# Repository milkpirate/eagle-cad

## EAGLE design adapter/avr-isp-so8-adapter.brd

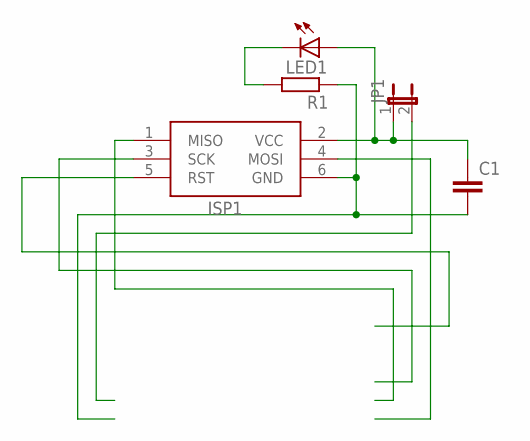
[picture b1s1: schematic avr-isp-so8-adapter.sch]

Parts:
C1: C-EUC0805K; C0805K
ISP1: AVRISP-6; AVRISP
JP1: JUMPER-2SMD-NO; SJ_2S-NO
LED1: LEDCHIPLED_0805; CHIPLED_0805
R1: R-EU_R0805; R0805

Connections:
unnamed: C1.2, ISP1.6 (GND), R1.1
unnamed: LED1.C, R1.2
VCC: C1.1, ISP1.2 (VCC), JP1.1, LED1.A

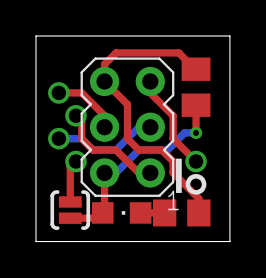
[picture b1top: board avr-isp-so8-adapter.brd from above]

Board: 2 copper layers, 10.8 x 11.4 mm, 5 parts (0 on the bottom side), 3 nets.

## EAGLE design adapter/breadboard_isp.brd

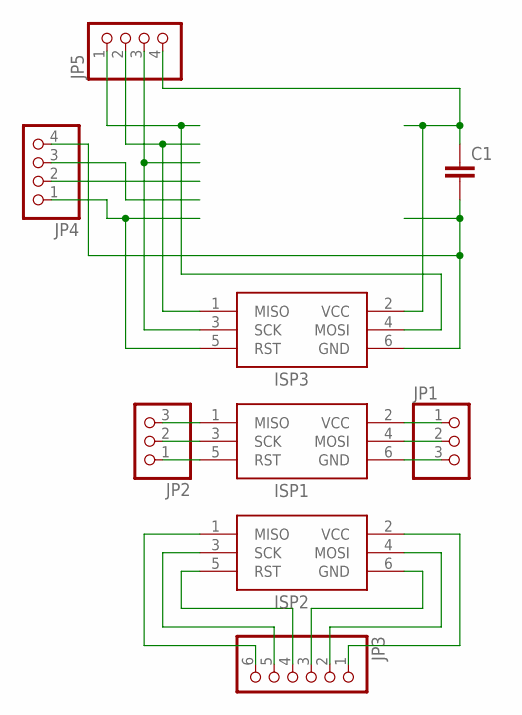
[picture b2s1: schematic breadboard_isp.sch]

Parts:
C1: C-EU025-025X050; C025-025X050
ISP1, ISP2, ISP3: AVRISP-6; AVRISP
JP1, JP2: PINHD-1X3; 1X03
JP3: PINHD-1X6; 1X06
JP4, JP5: PINHD-1X4; 1X04

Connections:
unnamed: ISP1.5 (RST), JP2.1
unnamed: ISP1.3 (SCK), JP2.2
unnamed: ISP1.1 (MISO), JP2.3
unnamed: ISP1.2 (VCC), JP1.1
unnamed: ISP1.4 (MOSI), JP1.2
unnamed: ISP1.6 (GND), JP1.3
unnamed: ISP2.5 (RST), JP3.4
unnamed: ISP2.6 (GND), JP3.3
unnamed: ISP2.4 (MOSI), JP3.2
unnamed: ISP2.3 (SCK), JP3.5
unnamed: ISP2.1 (MISO), JP3.6
unnamed: ISP2.2 (VCC), JP3.1
unnamed: C1.1, ISP3.2 (VCC), JP5.4
unnamed: C1.2, ISP3.6 (GND), JP4.4
unnamed: ISP3.4 (MOSI), JP5.1
unnamed: ISP3.1 (MISO), JP5.2
unnamed: ISP3.3 (SCK), JP5.3
unnamed: ISP3.5 (RST), JP4.1

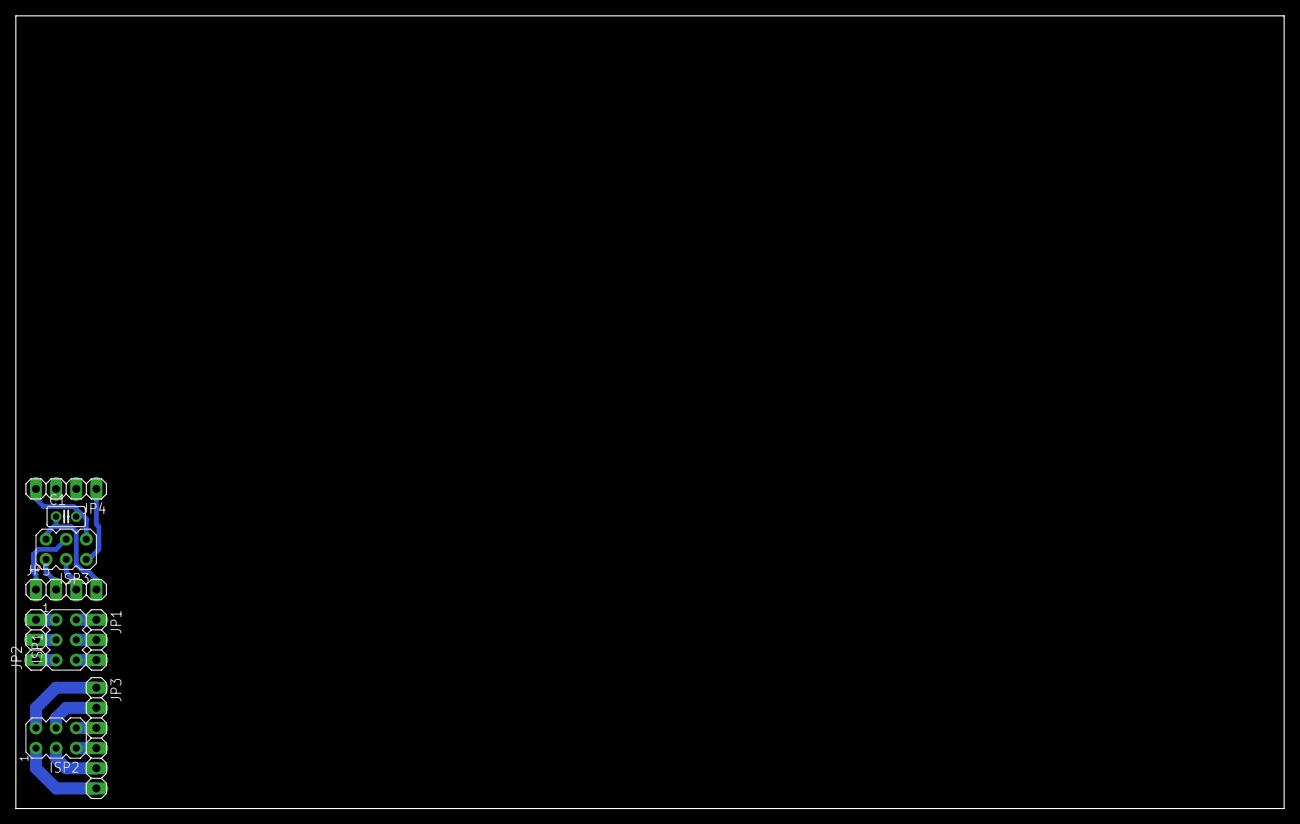
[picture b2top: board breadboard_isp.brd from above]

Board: 2 copper layers, 160.0 x 100.0 mm, 9 parts (0 on the bottom side), 18 nets.

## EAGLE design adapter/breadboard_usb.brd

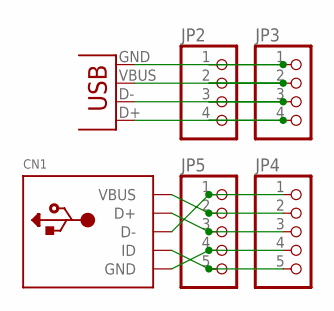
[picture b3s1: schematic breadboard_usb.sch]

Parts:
CN1: USBTHM; USB-MINIB-THM
JP1: USB-B; USB-B-PTH
JP2, JP3: PINHD-1X4; 1X04
JP4, JP5: PINHD-1X5; 1X05

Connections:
D+: CN1.D+, JP4.3, JP5.3
D-: CN1.D-, JP4.1, JP5.1
GND: CN1.GND, JP4.4, JP5.4
ID: CN1.ID, JP4.5, JP5.5
unnamed: JP1.GND, JP2.1, JP3.1
unnamed: JP1.VBUS, JP2.2, JP3.2
unnamed: JP1.D-, JP2.3, JP3.3
unnamed: JP1.D+, JP2.4, JP3.4
VUSB: CN1.VBUS, JP4.2, JP5.2

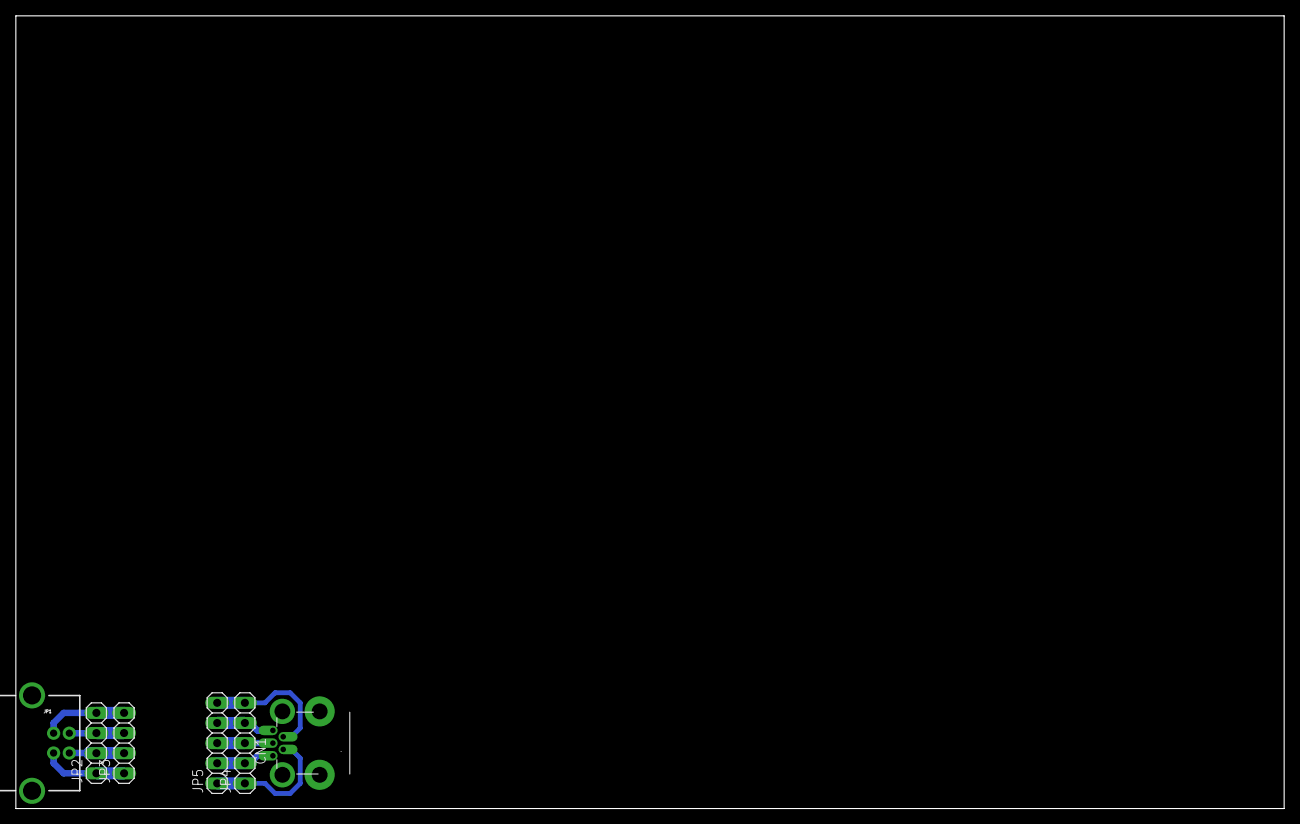
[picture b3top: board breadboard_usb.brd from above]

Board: 2 copper layers, 160.0 x 100.0 mm, 6 parts (0 on the bottom side), 9 nets.

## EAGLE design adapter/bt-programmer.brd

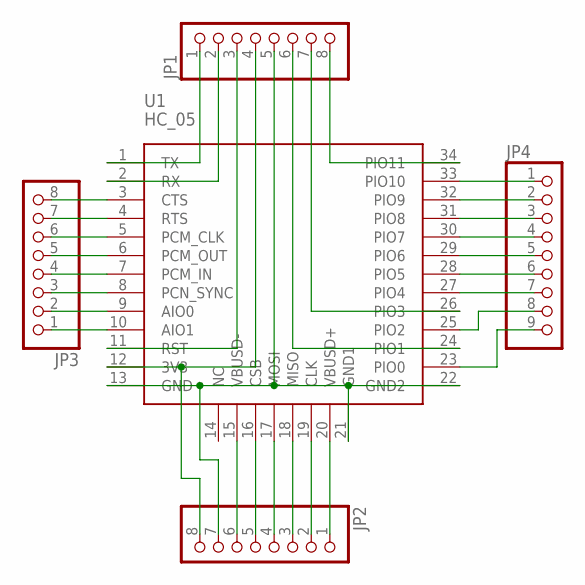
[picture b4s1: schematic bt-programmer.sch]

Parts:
JP1, JP2, JP3: PINHD-1X8; 1X08
JP4: PINHD-1X9; 1X09
U1: HC_05; BLUETOOTH_SMD

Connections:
unnamed: JP1.1, U1.1 (TX)
unnamed: JP1.2, U1.2 (RX)
unnamed: JP1.4, JP2.8, U1.12 (3V3)
unnamed: JP1.5, JP2.7, U1.13 (GND), U1.21 (GND1), U1.22 (GND2)
unnamed: JP1.3, U1.11 (RST)
unnamed: JP1.8, U1.34 (PIO11)
unnamed: JP1.7, U1.26 (PIO3)
unnamed: JP1.6, U1.24 (PIO1)
unnamed: JP2.6, U1.15 (VBUSD-)
unnamed: JP2.5, U1.16 (CSB)
unnamed: JP2.4, U1.17 (MOSI)
unnamed: JP2.3, U1.18 (MISO)
unnamed: JP2.2, U1.19 (CLK)
unnamed: JP2.1, U1.20 (VBUSD+)
unnamed: JP3.1, U1.10 (AIO1)
unnamed: JP3.2, U1.9 (AIO0)
unnamed: JP3.3, U1.8 (PCN_SYNC)
unnamed: JP3.4, U1.7 (PCM_IN)
unnamed: JP3.5, U1.6 (PCM_OUT)
unnamed: JP3.6, U1.5 (PCM_CLK)
unnamed: JP3.7, U1.4 (RTS)
unnamed: JP3.8, U1.3 (CTS)
unnamed: JP4.1, U1.33 (PIO10)
unnamed: JP4.2, U1.32 (PIO9)
unnamed: JP4.3, U1.31 (PIO8)
unnamed: JP4.4, U1.30 (PIO7)
unnamed: JP4.5, U1.29 (PIO6)
unnamed: JP4.6, U1.28 (PIO5)
unnamed: JP4.7, U1.27 (PIO4)
unnamed: JP4.8, U1.25 (PIO2)
unnamed: JP4.9, U1.23 (PIO0)

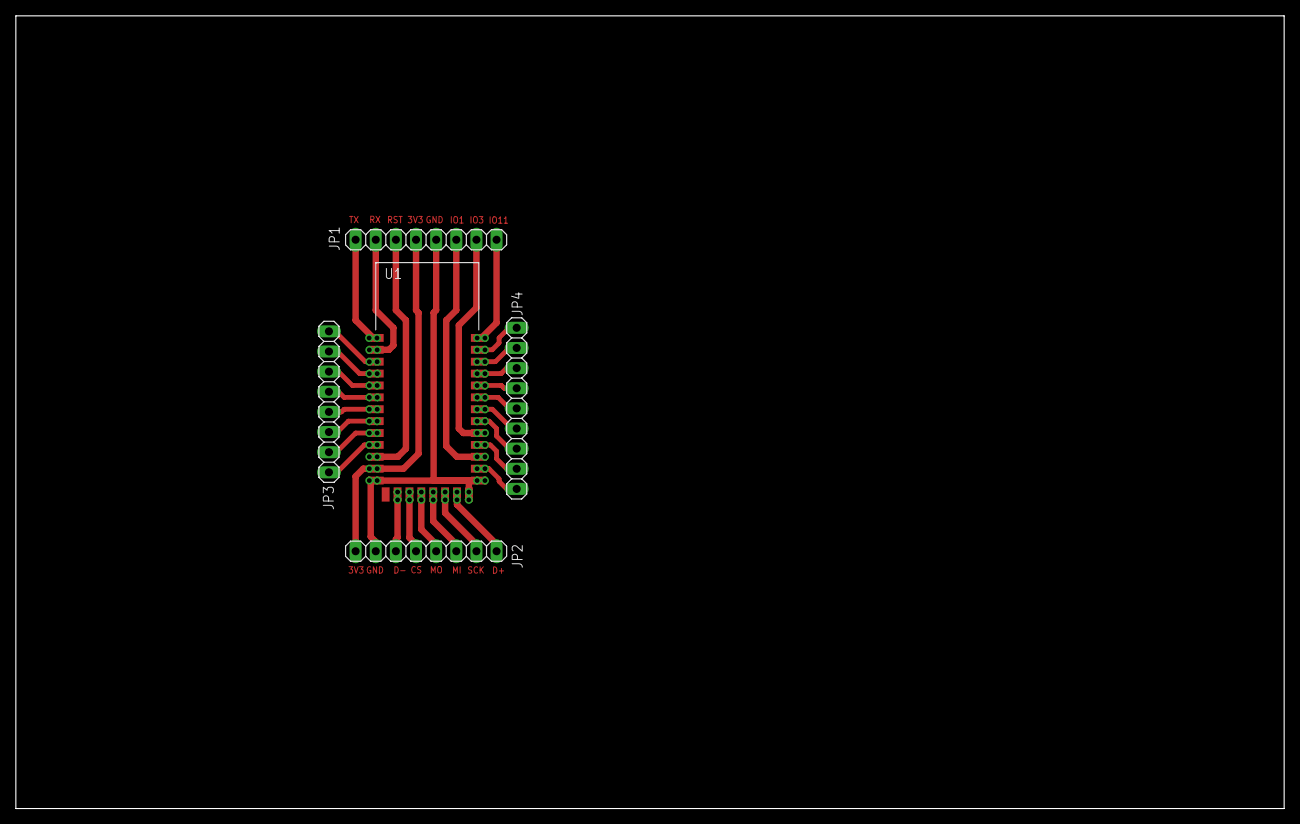
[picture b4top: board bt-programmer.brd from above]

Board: 2 copper layers, 160.0 x 100.0 mm, 5 parts (0 on the bottom side), 31 nets.

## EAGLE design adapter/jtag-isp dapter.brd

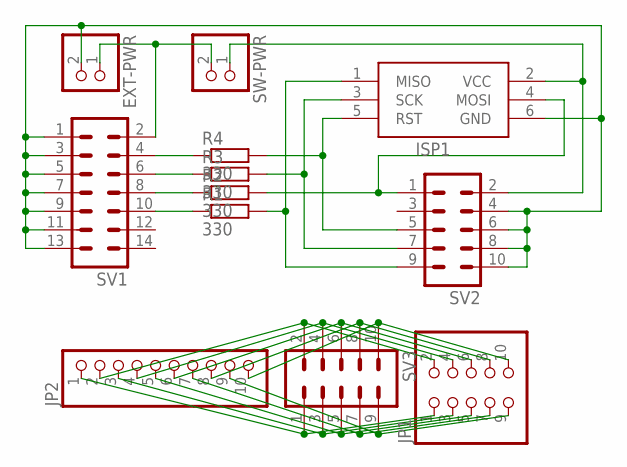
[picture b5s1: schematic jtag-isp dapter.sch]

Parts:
EXT-PWR: PINHD-1X2; 1X02
ISP1: AVRISP-6; AVRISP
JP1: PINHD-2X5; 2X05
JP2: PINHD-1X10; 1X10
R1, R2, R3, R4: 330; 0204/7
SV1: ML14
SV2, SV3: ML10
SW-PWR: PINHD-1X2; 1X02

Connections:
unnamed: JP1.1, JP2.1, SV3.1
unnamed: JP1.3, JP2.3, SV3.3
unnamed: JP1.5, JP2.5, SV3.5
unnamed: JP1.7, JP2.7, SV3.7
unnamed: JP1.9, JP2.9, SV3.9
unnamed: JP1.2, JP2.2, SV3.2
unnamed: JP1.4, JP2.4, SV3.4
unnamed: JP1.6, JP2.6, SV3.6
unnamed: JP1.8, JP2.8, SV3.8
unnamed: JP1.10, JP2.10, SV3.10
unnamed: EXT-PWR.2, ISP1.6 (GND), SV1.1, SV1.3, SV1.5, SV1.7, SV1.9, SV1.11, SV1.13, SV2.4, SV2.6, SV2.8, SV2.10
unnamed: ISP1.4 (MOSI), R2.2, SV2.1
unnamed: ISP1.5 (RST), R4.2, SV2.5
unnamed: ISP1.3 (SCK), R3.2, SV2.7
unnamed: ISP1.1 (MISO), R1.2, SV2.9
unnamed: R1.1, SV1.10
unnamed: R2.1, SV1.8
unnamed: R3.1, SV1.6
unnamed: R4.1, SV1.4
unnamed: EXT-PWR.1, SV1.2, SW-PWR.2
VCC: ISP1.2 (VCC), SV2.2, SW-PWR.1

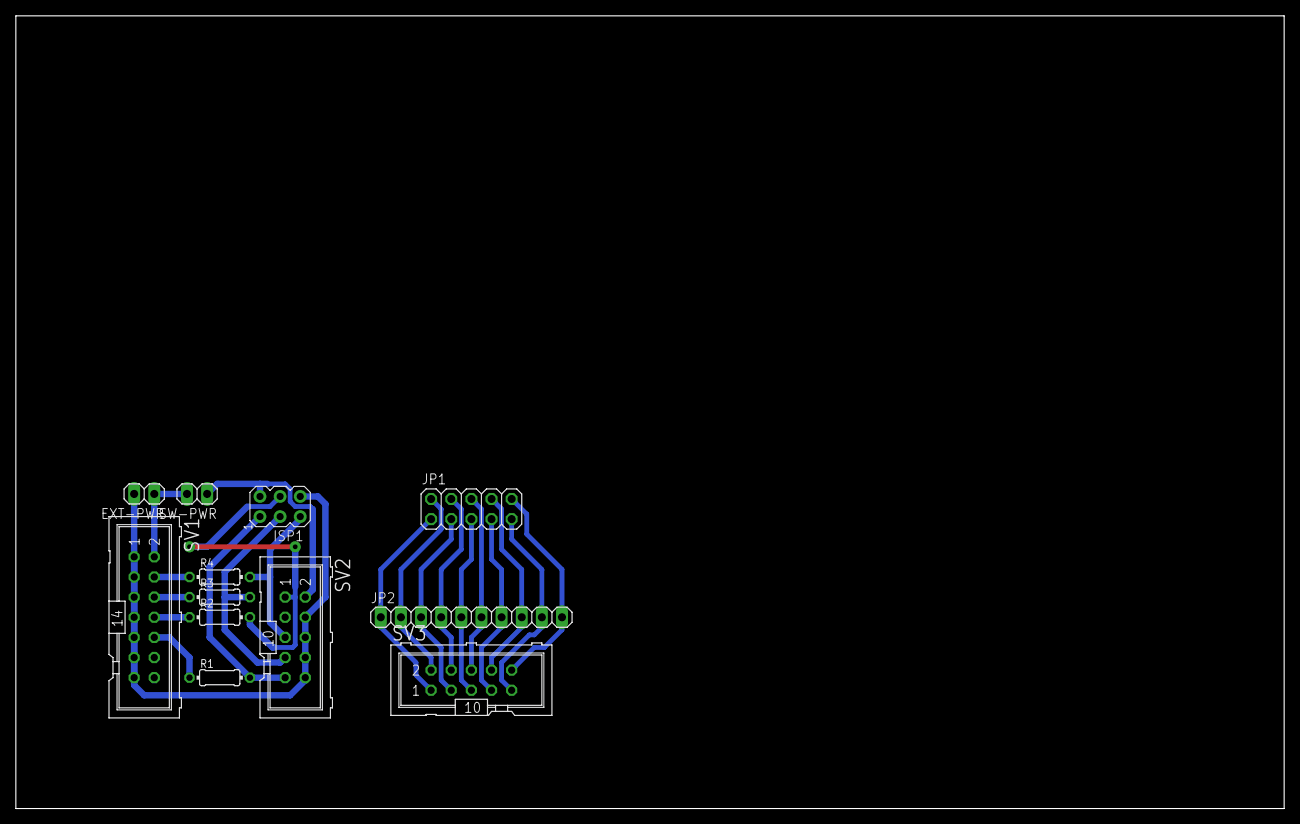
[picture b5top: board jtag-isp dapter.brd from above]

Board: 2 copper layers, 160.0 x 100.0 mm, 12 parts (0 on the bottom side), 21 nets.

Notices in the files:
parts and their libraries:
SparkFun-Retired: Licensing:Creative Commons ShareAlike 4.0 International - https://creativecommons.org/licenses/by-sa/4.0
SparkFun-Connectors: Licensing: CC v3.0 Share-Alike You are welcome to use this library for commercial purposes.
